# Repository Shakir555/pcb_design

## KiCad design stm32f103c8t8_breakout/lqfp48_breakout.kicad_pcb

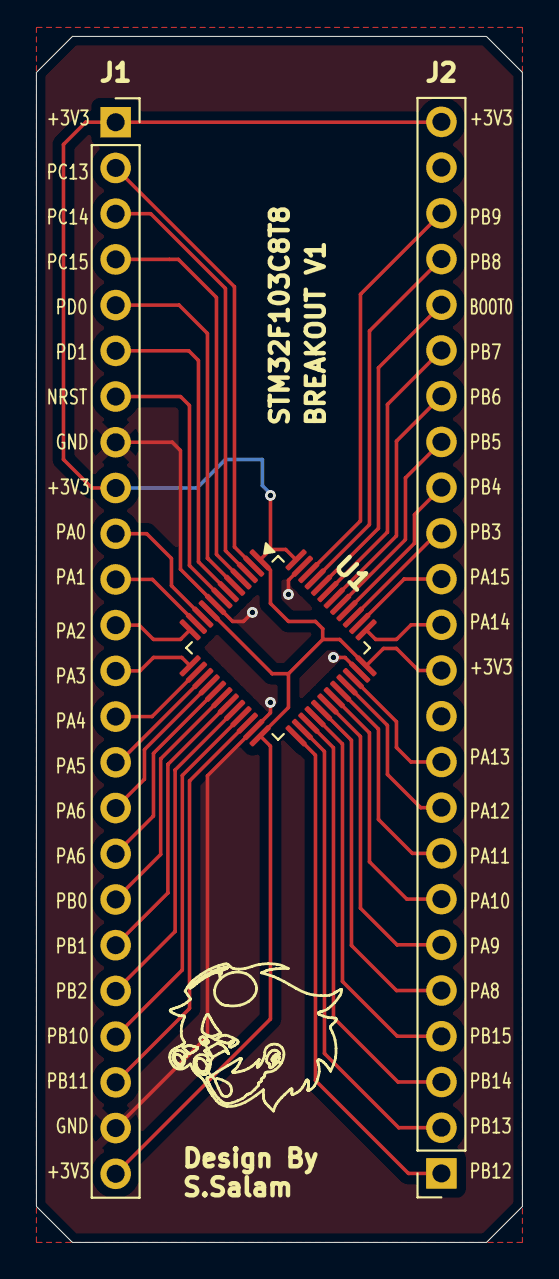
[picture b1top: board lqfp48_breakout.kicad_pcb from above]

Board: 2 copper layers, 27.0 x 67.0 mm, 4 parts (1 on the bottom side), 41 nets.

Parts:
C1: 100nF; C_0805_2012Metric
J1, J2: Conn_01x24; PinSocket_1x24_P2.54mm_Vertical
U1: STM32F103C8T8; LQFP-48_7x7mm_P0.5mm

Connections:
+3V3: C1.1, J1.1, J1.9, J1.24, J2.12, J2.24, U1.1 (VBAT), U1.9 (VDDA), U1.24 (VDD), U1.36 (VDD), U1.48 (VDD)
/BOOT0: J2.20, U1.44 (BOOT0)
/NRST: J1.7, U1.7 (NRST)
/PA0: J1.10, U1.10 (PA0)
/PA1: J1.11, U1.11 (PA1)
/PA2: J1.12, U1.12 (PA2)
/PA3: J1.13, U1.13 (PA3)
/PA4: J1.14, U1.14 (PA4)
/PA5: J1.15, U1.15 (PA5)
/PA6: J1.16, U1.16 (PA6)
/PA7: J1.17, U1.17 (PA7)
/PA8: J2.5, U1.29 (PA8)
/PA9: J2.6, U1.30 (PA9)
/PA10: J2.7, U1.31 (PA10)
/PA11: J2.8, U1.32 (PA11)
/PA12: J2.9, U1.33 (PA12)
/PA13: J2.10, U1.34 (PA13)
/PA14: J2.13, U1.37 (PA14)
/PA15: J2.14, U1.38 (PA15)
/PB0: J1.18, U1.18 (PB0)
/PB1: J1.19, U1.19 (PB1)
/PB2: J1.20, U1.20 (PB2)
/PB3: J2.15, U1.39 (PB3)
/PB4: J2.16, U1.40 (PB4)
/PB5: J2.17, U1.41 (PB5)
/PB6: J2.18, U1.42 (PB6)
/PB7: J2.19, U1.43 (PB7)
/PB8: J2.21, U1.45 (PB8)
/PB9: J2.22, U1.46 (PB9)
/PB10: J1.21, U1.21 (PB10)
/PB11: J1.22, U1.22 (PB11)
/PB12: J2.1, U1.25 (PB12)
/PB13: J2.2, U1.26 (PB13)
/PB14: J2.3, U1.27 (PB14)
/PB15: J2.4, U1.28 (PB15)
/PC13: J1.2, U1.2 (PC13)
/PC14: J1.3, U1.3 (PC14)
/PC15: J1.4, U1.4 (PC15)
/PD0: J1.5, U1.5 (PD0)
/PD1: J1.6, U1.6 (PD1)
GND: C1.2, J1.8, J1.23, U1.8 (VSSA), U1.23 (VSS), U1.35 (VSS), U1.47 (VSS)

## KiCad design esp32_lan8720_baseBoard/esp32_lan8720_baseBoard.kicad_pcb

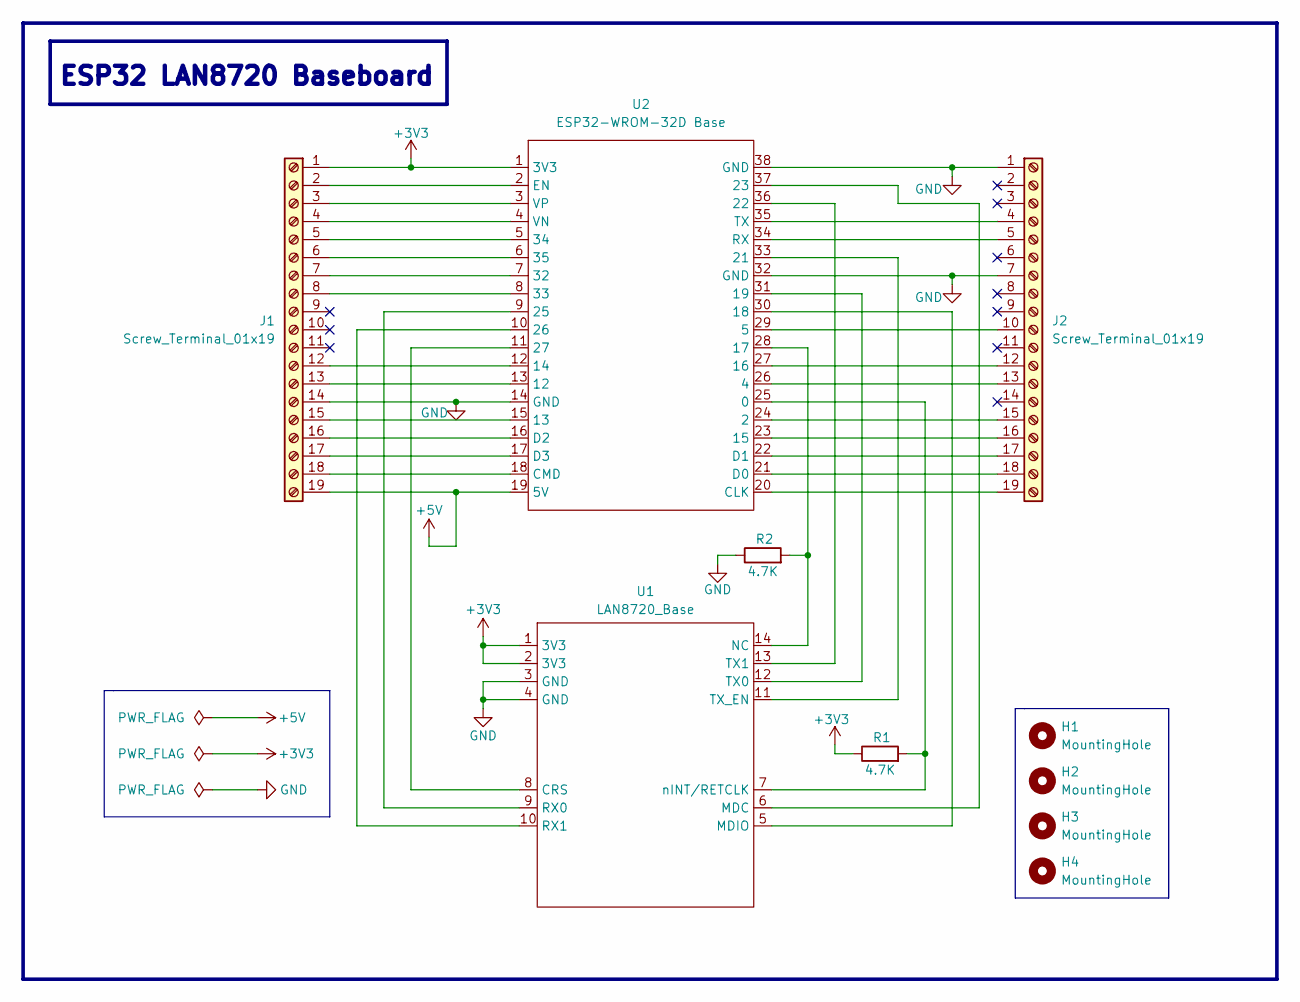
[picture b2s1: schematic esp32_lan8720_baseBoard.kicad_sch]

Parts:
H1, H2, H3, H4: MountingHole; MountingHole_3.2mm_M3
J1, J2: Screw_Terminal_01x19; terminal_block_01x19_5.08mm
R1, R2: 4.7K; R_0805_2012Metric_Pad1.20x1.40mm_HandSolder
U1: LAN8720_Base; lan8720_base
U2: ESP32-WROM-32D Base; esp32_wrom_32d_base

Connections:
+3V3: J1.1, R1.1, U1.1 (3V3), U1.2 (3V3), U2.1 (3V3)
+5V: J1.19, U2.19 (5V)
GND: J1.14, J2.1, J2.7, R2.1, U1.3 (GND), U1.4 (GND), U2.14 (GND), U2.32 (GND), U2.38 (GND)
unnamed: J1.2, U2.2 (EN)
unnamed: J1.3, U2.3 (VP)
unnamed: J1.4, U2.4 (VN)
unnamed: J1.5, U2.5 (34)
unnamed: J1.6, U2.6 (35)
unnamed: J1.7, U2.7 (32)
unnamed: J1.8, U2.8 (33)
unnamed: J1.12, U2.12 (14)
unnamed: J1.13, U2.13 (12)
unnamed: J1.15, U2.15 (13)
unnamed: J1.16, U2.16 (D2)
unnamed: J1.17, U2.17 (D3)
unnamed: J1.18, U2.18 (CMD)
unnamed: J2.4, U2.35 (TX)
unnamed: J2.5, U2.34 (RX)
unnamed: J2.10, U2.29 (5)
unnamed: J2.12, U2.27 (16)
unnamed: J2.13, U2.26 (4)
unnamed: J2.15, U2.24 (2)
unnamed: J2.16, U2.23 (15)
unnamed: J2.17, U2.22 (D1)
unnamed: J2.18, U2.21 (D0)
unnamed: J2.19, U2.20 (CLK)
unnamed: U1.8 (CRS), U2.11 (27)
unnamed: U1.6 (MDC), U2.37 (23)
unnamed: U1.5 (MDIO), U2.30 (18)
unnamed: R2.2, U1.14 (NC), U2.28 (17)
unnamed: U1.9 (RX0), U2.9 (25)
unnamed: U1.10 (RX1), U2.10 (26)
unnamed: U1.12 (TX0), U2.31 (19)
unnamed: U1.13 (TX1), U2.36 (22)
unnamed: U1.11 (TX_EN), U2.33 (21)
unnamed: R1.2, U1.7 (nINT/RETCLK), U2.25 (0)

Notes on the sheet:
ESP32 LAN8720 Baseboard

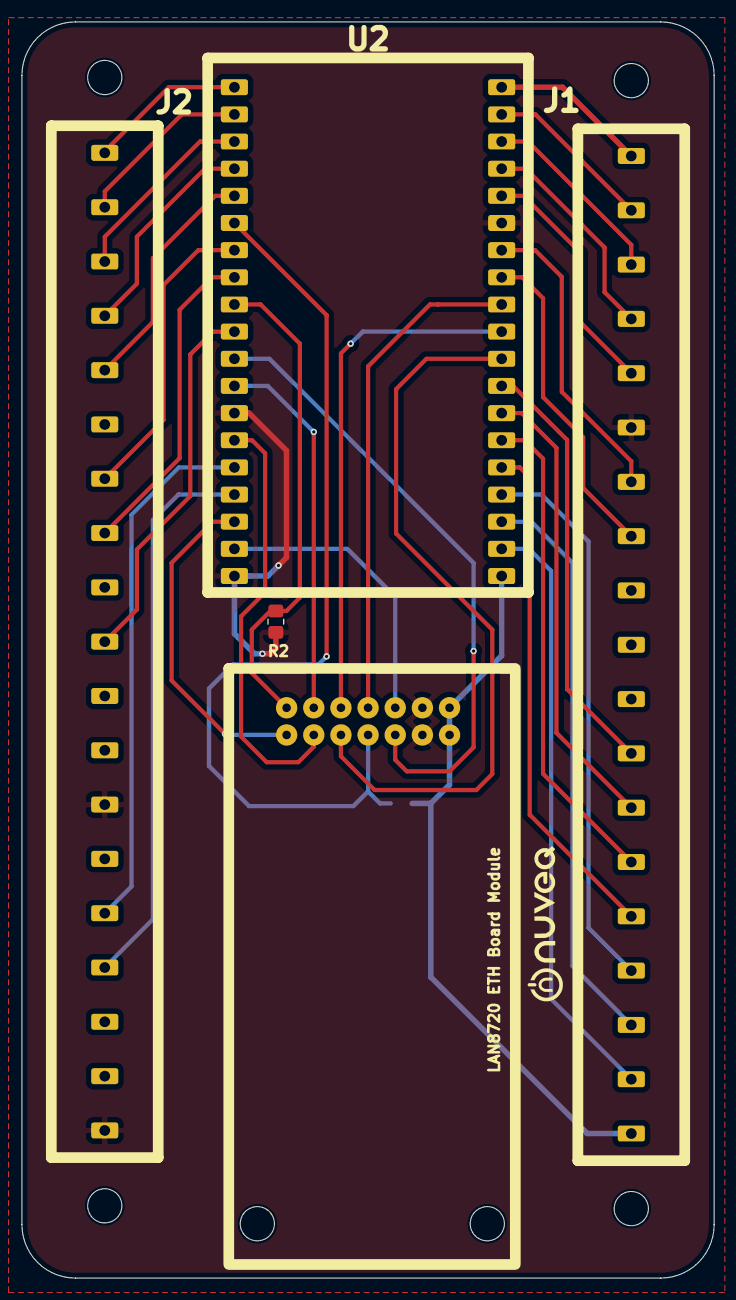
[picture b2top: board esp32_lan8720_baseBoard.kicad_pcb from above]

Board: 2 copper layers, 64.8 x 117.5 mm, 10 parts (1 on the bottom side), 36 nets.

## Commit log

2026-04-22 5V to 3V3 Regulated Power Supply
2026-04-22 STM32F103C8T6 White Pill
2026-04-22 ESP32 LAN8720 BaseBoard
2026-04-22 Remove ESP32 LAN8720 BaseBoard
2026-04-22 USB C Conn Power Breakout
2026-04-22 stm32f103c8t8 breakout
